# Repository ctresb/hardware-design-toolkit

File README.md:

<p align="center">
  <a href="#install">Install</a> ·
  <a href="#how-it-works">How it works</a> ·
  <a href="#the-skills">Skills</a> ·
  <a href="examples/pocket-beacon">Example</a> ·
  <a href="CONVENTIONS.md">Conventions</a>
</p>

---

The Hardware Design Toolkit is a set of [Claude Code](https://code.claude.com) skills. They take an idea
for an electronic device to a design that a factory can build. You describe what you want. Claude
interviews you, picks real parts and checks that they can be bought. It sizes a battery that exists, lays
out the board in KiCad and models the enclosure in CAD. It validates that nothing collides, renders the
product, draws the blueprint and prices it from 1 to 10,000 units. It lists the certifications and plans
the prototypes. Then it attacks its own design until nothing fixable is left.

The output is a **READY TO BUILD** package:

- a routed board with fab files;
- a BOM that is in stock;
- enclosure STEP files;
- an assembly guide and a test plan;
- an `ORDER.md` that says what to upload where;
- a presentation that explains the product.

## Why

A beautiful render of a device is easy. It is harder to make a device that is real. In practice the
problems look like this:

- The battery in the render has twice the capacity that a real cell of that size can hold.
- The chip is "Active" at the distributor but still sampling at the manufacturer.
- The LED driver needs 2.5 V and sits on a 1.8 V rail.
- The microphone is bottom-port and the design has no hole.
- The board was never routed.

Every rule in this toolkit comes from a mistake like these, made and corrected while a real wearable was
designed. Each skill checks for those mistakes with a script, not with good intentions.

## Quick Start

1. Install the plugin in Claude Code (or clone the repository for any agent runtime):
   ```text
   /plugin marketplace add ctresb/hardware-design-toolkit
   /plugin install hardware-design@hardware-design-toolkit
   ```
2. Launch a hardware project in an empty folder:
   ```text
   /hardware-design:hardware-engineer I want to build a small Bluetooth tag that beeps when I lose my keys
   ```
3. Verify the reference example (`examples/pocket-beacon`) from the terminal:
   ```sh
   python3 skills/doability-review/scripts/doability_score.py --hw examples/pocket-beacon/hw
   python3 skills/build-package/scripts/selftest.py
   ```
   See [docs/hardening-and-dfm-gates.md](docs/hardening-and-dfm-gates.md) for the physics, electrical, RF, and CAD verification gates.

## Install

In Claude Code:

```text
/plugin marketplace add ctresb/hardware-design-toolkit
/plugin install hardware-design@hardware-design-toolkit
```

Then start a project in an empty folder:

```text
/hardware-design:hardware-engineer I want to build a small Bluetooth tag that beeps when I lose my keys
```

The first run checks your machine and offers to install what is missing (`toolchain-setup`). Nothing is
installed without your consent.

<details>
<summary>Manual install (copy the skills)</summary>

```sh
git clone https://github.com/ctresb/hardware-design-toolkit
cp -R hardware-design-toolkit/skills/* ~/.claude/skills/
```

Copy every skill folder. The skills call each other's scripts through relative paths.
</details>

### Software it uses

| Tool | Used for | Required |
|---|---|---|
| [KiCad](https://www.kicad.org) 9 or 10 | schematic, PCB, DRC, fab outputs | yes, for PCB stages |
| [Freerouting](https://github.com/freerouting/freerouting) + Java 21+ | autorouting | for routing |
| [Blender](https://www.blender.org) 5.x | assembly validation, renders, blueprints | yes, for visual stages |
| [build123d](https://github.com/gumyr/build123d) (Python 3.10–3.13) | parametric enclosure CAD, STEP export | yes, for enclosure stages |
| Python 3.10+ | all scripts | yes |
| librsvg (`rsvg-convert`) | SVG to PDF/PNG | yes |
| Chrome or Chromium | presentation layout check and PDF | recommended |
| KiKit, FreeCAD, ffmpeg, ImageMagick | panels, STEP viewing, turntables, photos | optional |
| AWS CLI + Session Manager plugin | cloud GPU rendering | optional |

`toolchain-setup` installs these on macOS (Homebrew), Linux (apt, dnf or Flatpak) and Windows (winget).
It then writes the resolved paths to `toolchain.json` for the other skills.

## How it works

### Architecture

```mermaid
flowchart LR
  A[Interview] --> B[Specs and parts]
  B --> C[Part research]
  B --> D[Power and battery]
  C --> E{Paper review}
  D --> E
  E --> F[Enclosure CAD]
  E --> G[PCB]
  F <--> G
  F --> H{Assembly validation}
  G --> H
  H --> I[Renders and blueprint]
  H --> J[Cost, certification, roadmap]
  I --> K{Final review and fix loop}
  J --> K
  K -->|fixable findings| B
  K --> L[Build package]
  L --> M[Presentation]
```

All skills share one workspace in your project, `hw/`. Each file there has exactly one owner skill, and
every number carries its evidence: `verified` with a dated source, `estimate` with its basis, or
`assumption`. The contract is in [CONVENTIONS.md](CONVENTIONS.md).

Gates stop the pipeline when something is wrong:

- an unbuyable part;
- a rail outside a chip's supply range;
- a collision in the assembly;
- an unrouted board;
- a chart label crossing a line.

A finding that the toolkit can fix goes back to the skill that owns it, and the review runs again. Only
items that need you or the physical world stay open, for example a current measurement on the first
prototype. Each one comes with a method and a pass threshold.

## The skills

| Skill | What it does |
|---|---|
| [`hardware-engineer`](skills/hardware-engineer) | Leads the project: stages, gates, parallel work, the fix loop, state |
| [`product-discovery`](skills/product-discovery) | Interviews you about use, environment, size, power, markets and budget, and writes the brief |
| [`specs-engineer`](skills/specs-engineer) | Requirements, architecture, power rails and a part for every function; lints the BOM |
| [`electronics-researcher`](skills/electronics-researcher) | One dossier per part: datasheet facts, max dimensions, lifecycle, prices from 1 to 10k, stock, alternatives |
| [`battery-and-power`](skills/battery-and-power) | Power budget per mode, peak-current chain, and the largest real cell that fits your space |
| [`pcb-engineer`](skills/pcb-engineer) | Generates the KiCad schematic and board from a spec, with legalized placement and keepouts, ERC/DRC, routing and fab outputs |
| [`enclosure-engineer`](skills/enclosure-engineer) | build123d enclosure with DFM checks, STEP export, tolerance stack, sealing; validates the assembly in Blender |
| [`product-render`](skills/product-render) | Photoreal Cycles renders: studio recipes, worn materials, physical solder fillets, cloud GPU guide |
| [`technical-drawing`](skills/technical-drawing) | Vector exploded blueprint with BOM balloons and orthographic views with dimensions |
| [`cost-and-sourcing`](skills/cost-and-sourcing) | Unit cost from 1 to 10k units, one-time costs separated, landed cost per country, suppliers, RFQs |
| [`compliance-planner`](skills/compliance-planner) | Certifications per market (radio, battery, safety, privacy) with cost and lead time |
| [`prototype-roadmap`](skills/prototype-roadmap) | Dev kit to EVT, DVT, PVT and mass production, with the critical path and long-lead orders |
| [`doability-review`](skills/doability-review) | The red team: checks everything again, sends fixes to their owners, and gives the final verdict |
| [`build-package`](skills/build-package) | Assembles the release (fab, assembly, purchasing, mech, test, order steps) and runs the ready-to-build gate |
| [`product-presentation`](skills/product-presentation) | A self-contained HTML deck of the product, with an automated layout check |
| [`lab-notebook`](skills/lab-notebook) | Facts, experiments, lessons and retros, so the project never goes backwards |
| [`toolchain-setup`](skills/toolchain-setup) | Finds, installs and verifies the software |

You can run any skill alone, for example `/hardware-design:doability-review` on a design you already have.

## Example

[`examples/pocket-beacon`](examples/pocket-beacon) is a complete run of the toolkit on a fictional
Bluetooth item finder that runs on a CR2032. It ends **READY TO BUILD (prototype)**:

- a routed 4-layer board with fab files;
- a 32 × 32 × 10 mm enclosure in STEP;
- 47 parts in stock with dated prices;
- a cost model from 10 to 10,000 units;
- a certification plan, a roadmap and a release package with the ordering steps.

The run also improved the toolkit. Each skill bug and missing rule it hit was fixed in the skills
([`docs/integration-report.md`](docs/integration-report.md)).

## Principles

1. **Real before pretty.** Parts are sized by the datasheet's maximum dimensions, never the nominal ones.
   Cells have straight edges and seals. A placeholder never pretends to be the product.
2. **Measure before you commit.** No custom cell, mold or board revision without a measured power budget or
   a dated plan to measure it.
3. **Evidence on every number.** Estimates are labeled, and every estimate comes with the quote or
   measurement that would replace it.
4. **Validate before you show.** No render, drawing or slide comes from an assembly that did not pass the
   validator. No visual leaves without an automated layout check.
5. **Fix, don't report.** The toolkit fixes what it can and asks only about what it cannot.

## Limits

- The toolkit plans certifications. It does not certify anything, and nothing here is legal advice.
- Prices and stock are snapshots with dates. Check them again before you order.
- RF matching, acoustic tuning and the final power numbers need a real prototype and real instruments. The
  toolkit tells you exactly what to measure and the pass values.
- **WARNING** Lithium cells can catch fire when punctured, shorted or charged wrong. Mains-powered designs
  can kill. Follow the safety notes in the skills, and have a qualified person review designs that involve
  either.

## Contributing

Read [CONVENTIONS.md](CONVENTIONS.md) first. A new rule needs the mistake that motivated it. A new script
needs a test that fails without it.

## License

[MIT](LICENSE). This is an independent community project, not affiliated with or endorsed by Anthropic.
"Claude" and "Claude Code" are trademarks of Anthropic.

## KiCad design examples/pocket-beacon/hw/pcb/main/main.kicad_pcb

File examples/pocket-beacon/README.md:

# Pocket Beacon: a complete run of the toolkit

Pocket Beacon is a fictional Bluetooth item finder for keys and bags. It beeps when the phone asks, runs
for more than a year on a CR2032, and is sealed to IP67. Every file in `hw/` was produced by the toolkit's
skills in one session: interview decisions, part research, power, KiCad board, CAD enclosure, validation,
renders, drawings, cost, certification, roadmap, review and release.

**Verdict: READY TO BUILD (prototype).** The board is routed and the fab files pass the release check. The
enclosure is in STEP and the assembly validates. 15 measurements remain for the built prototype, each with
a method and a pass threshold.

| | |
|---|---|
| Size | 32.0 × 32.0 × 10.0 mm, 4.3 g of plastic |
| Radio | TI CC2340R52 BLE SoC, chip antenna |
| Sound | Same Sky CPT-9019A piezo with PAM8904 driver, ≈ 78–80 dB at 25 cm [estimate] |
| Battery | CR2032 in a Keystone 3034TR holder, user-replaceable behind a tool-secured door (UL 4200A) |
| Battery life | 13 months calibrated on real trackers, 35 months bottom-up [estimate] |
| Board | 28.4 mm, 4 layers, 0.6 mm, 47 parts, DRC 0, ERC 0, every part with an LCSC number except the cell |
| Unit cost | US$ 51–153 at 10 units, US$ 8.89–17.1 at 1,000 units (FOB) |
| 10 EVT prototypes | US$ 800–1,800 in total, steps in [`ORDER.md`](hw/release/evt0-a/ORDER.md) |
| Certification | US$ 33k–128.5k for US, EU, UK and Brazil [estimate]; US first |
| First legal US sale | between 2027-05-10 and 2027-09-27 |

## What the toolkit found and fixed

The first parts list looked fine on paper. Research and review changed it:

- **4 of 23 first-choice parts could not be used.**
  - The piezo was last-time-buy.
  - The 48 MHz crystal had 4 units in stock.
  - An RF inductor was obsolete.
  - Two capacitors had no stock.
- **The 22 µF bulk capacitors keep 10.7 µF at 3 V.** A third capacitor was added to meet TI's
  supply-slew limit during the ring.
- **A loud ring on a cold, aged CR2032 browns out the chip.** The firmware rule now picks the ring level
  from the cell voltage under load.
- **Comparison with TI's reference board** found a missing VDDD capacitor and a missing harmonic filter.
- **A coin-cell bayonet did not fit in 10 mm.** The door uses captive screws instead, which still meets
  the US coin-cell law.
- **Assembler catalogs list look-alike parts under genuine part numbers.** Parts are ordered by catalog
  number, and the brand is checked.

## Where to look

| Folder | Content |
|---|---|
| [`hw/brief.md`](hw/brief.md), [`requirements.md`](hw/requirements.md), [`architecture.md`](hw/architecture.md) | What it is and how it works |
| [`hw/bom.csv`](hw/bom.csv), [`hw/parts/`](hw/parts) | The BOM and one dossier per part, with sources and dates |
| [`hw/power/`](hw/power) | Power budget, CR2032 behavior, measurement plan |
| [`hw/pcb/`](hw/pcb) | KiCad project, fab outputs, plots |
| [`hw/mech/`](hw/mech) | build123d CAD, STEP/STL, DFM, tolerances, validated assembly |
| [`hw/renders/`](hw/renders), [`hw/drawings/`](hw/drawings) | Cycles renders and the quotation blueprint |
| [`hw/cost/`](hw/cost), [`hw/compliance.md`](hw/compliance.md), [`hw/roadmap.md`](hw/roadmap.md) | Business |
| [`hw/doability/review.md`](hw/doability/review.md) | The adversarial review and the prototype checks |
| [`hw/release/evt0-a/`](hw/release/evt0-a) | The READY TO BUILD package |
| [`hw/presentation/index.html`](hw/presentation/index.html) | The presentation |
| [`hw/knowledge/`](hw/knowledge), [`hw/decisions.md`](hw/decisions.md), [`hw/retros/`](hw/retros) | How every decision was made |

## What is still open

- **Decisions taken in the product-owner role.** Each one is logged in `hw/decisions.md` for a real
  owner to confirm. Examples: the screw door, and launching in the US first.
- **Quotes.** Final assembly and molding costs decide whether the US$ 12 target at 1,000 units is met
  (`hw/cost/rfq.md`).
- **The 15 prototype measurements:** current, RF match, loudness, sealing and button continuity
  (`hw/doability/review.md`).

Pocket Beacon is fictional. Prices and stock are snapshots from 2026-11-08.

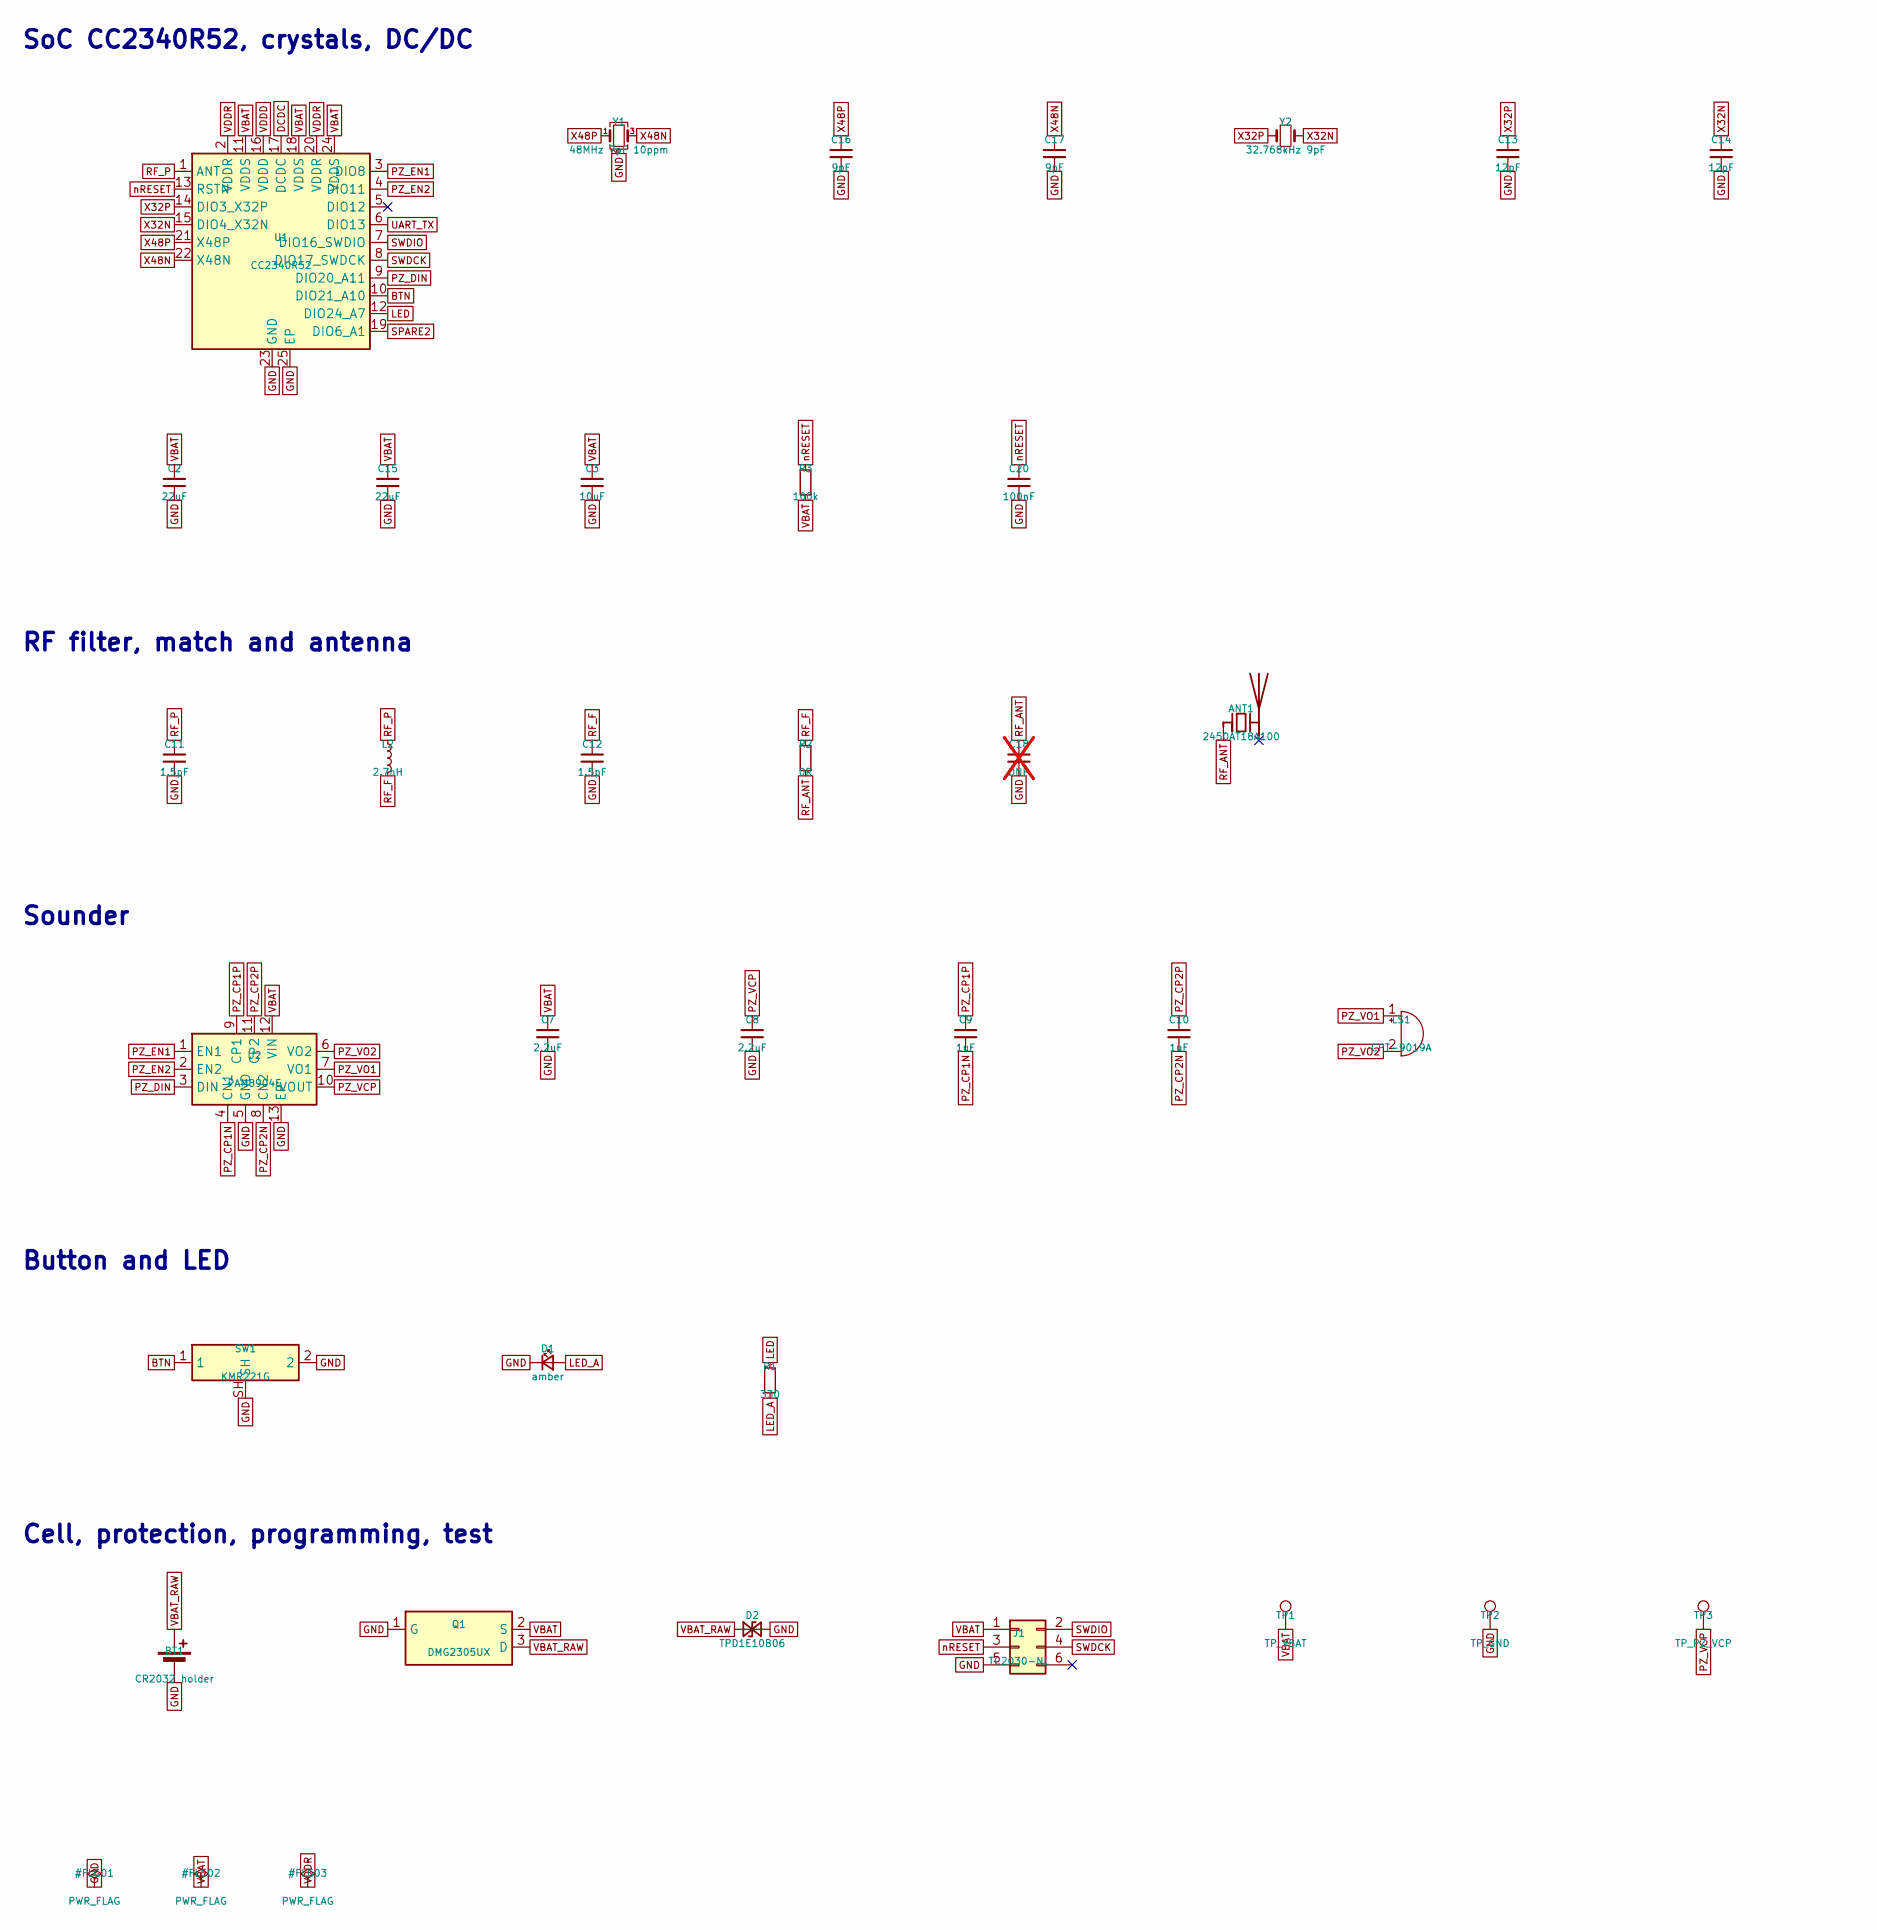
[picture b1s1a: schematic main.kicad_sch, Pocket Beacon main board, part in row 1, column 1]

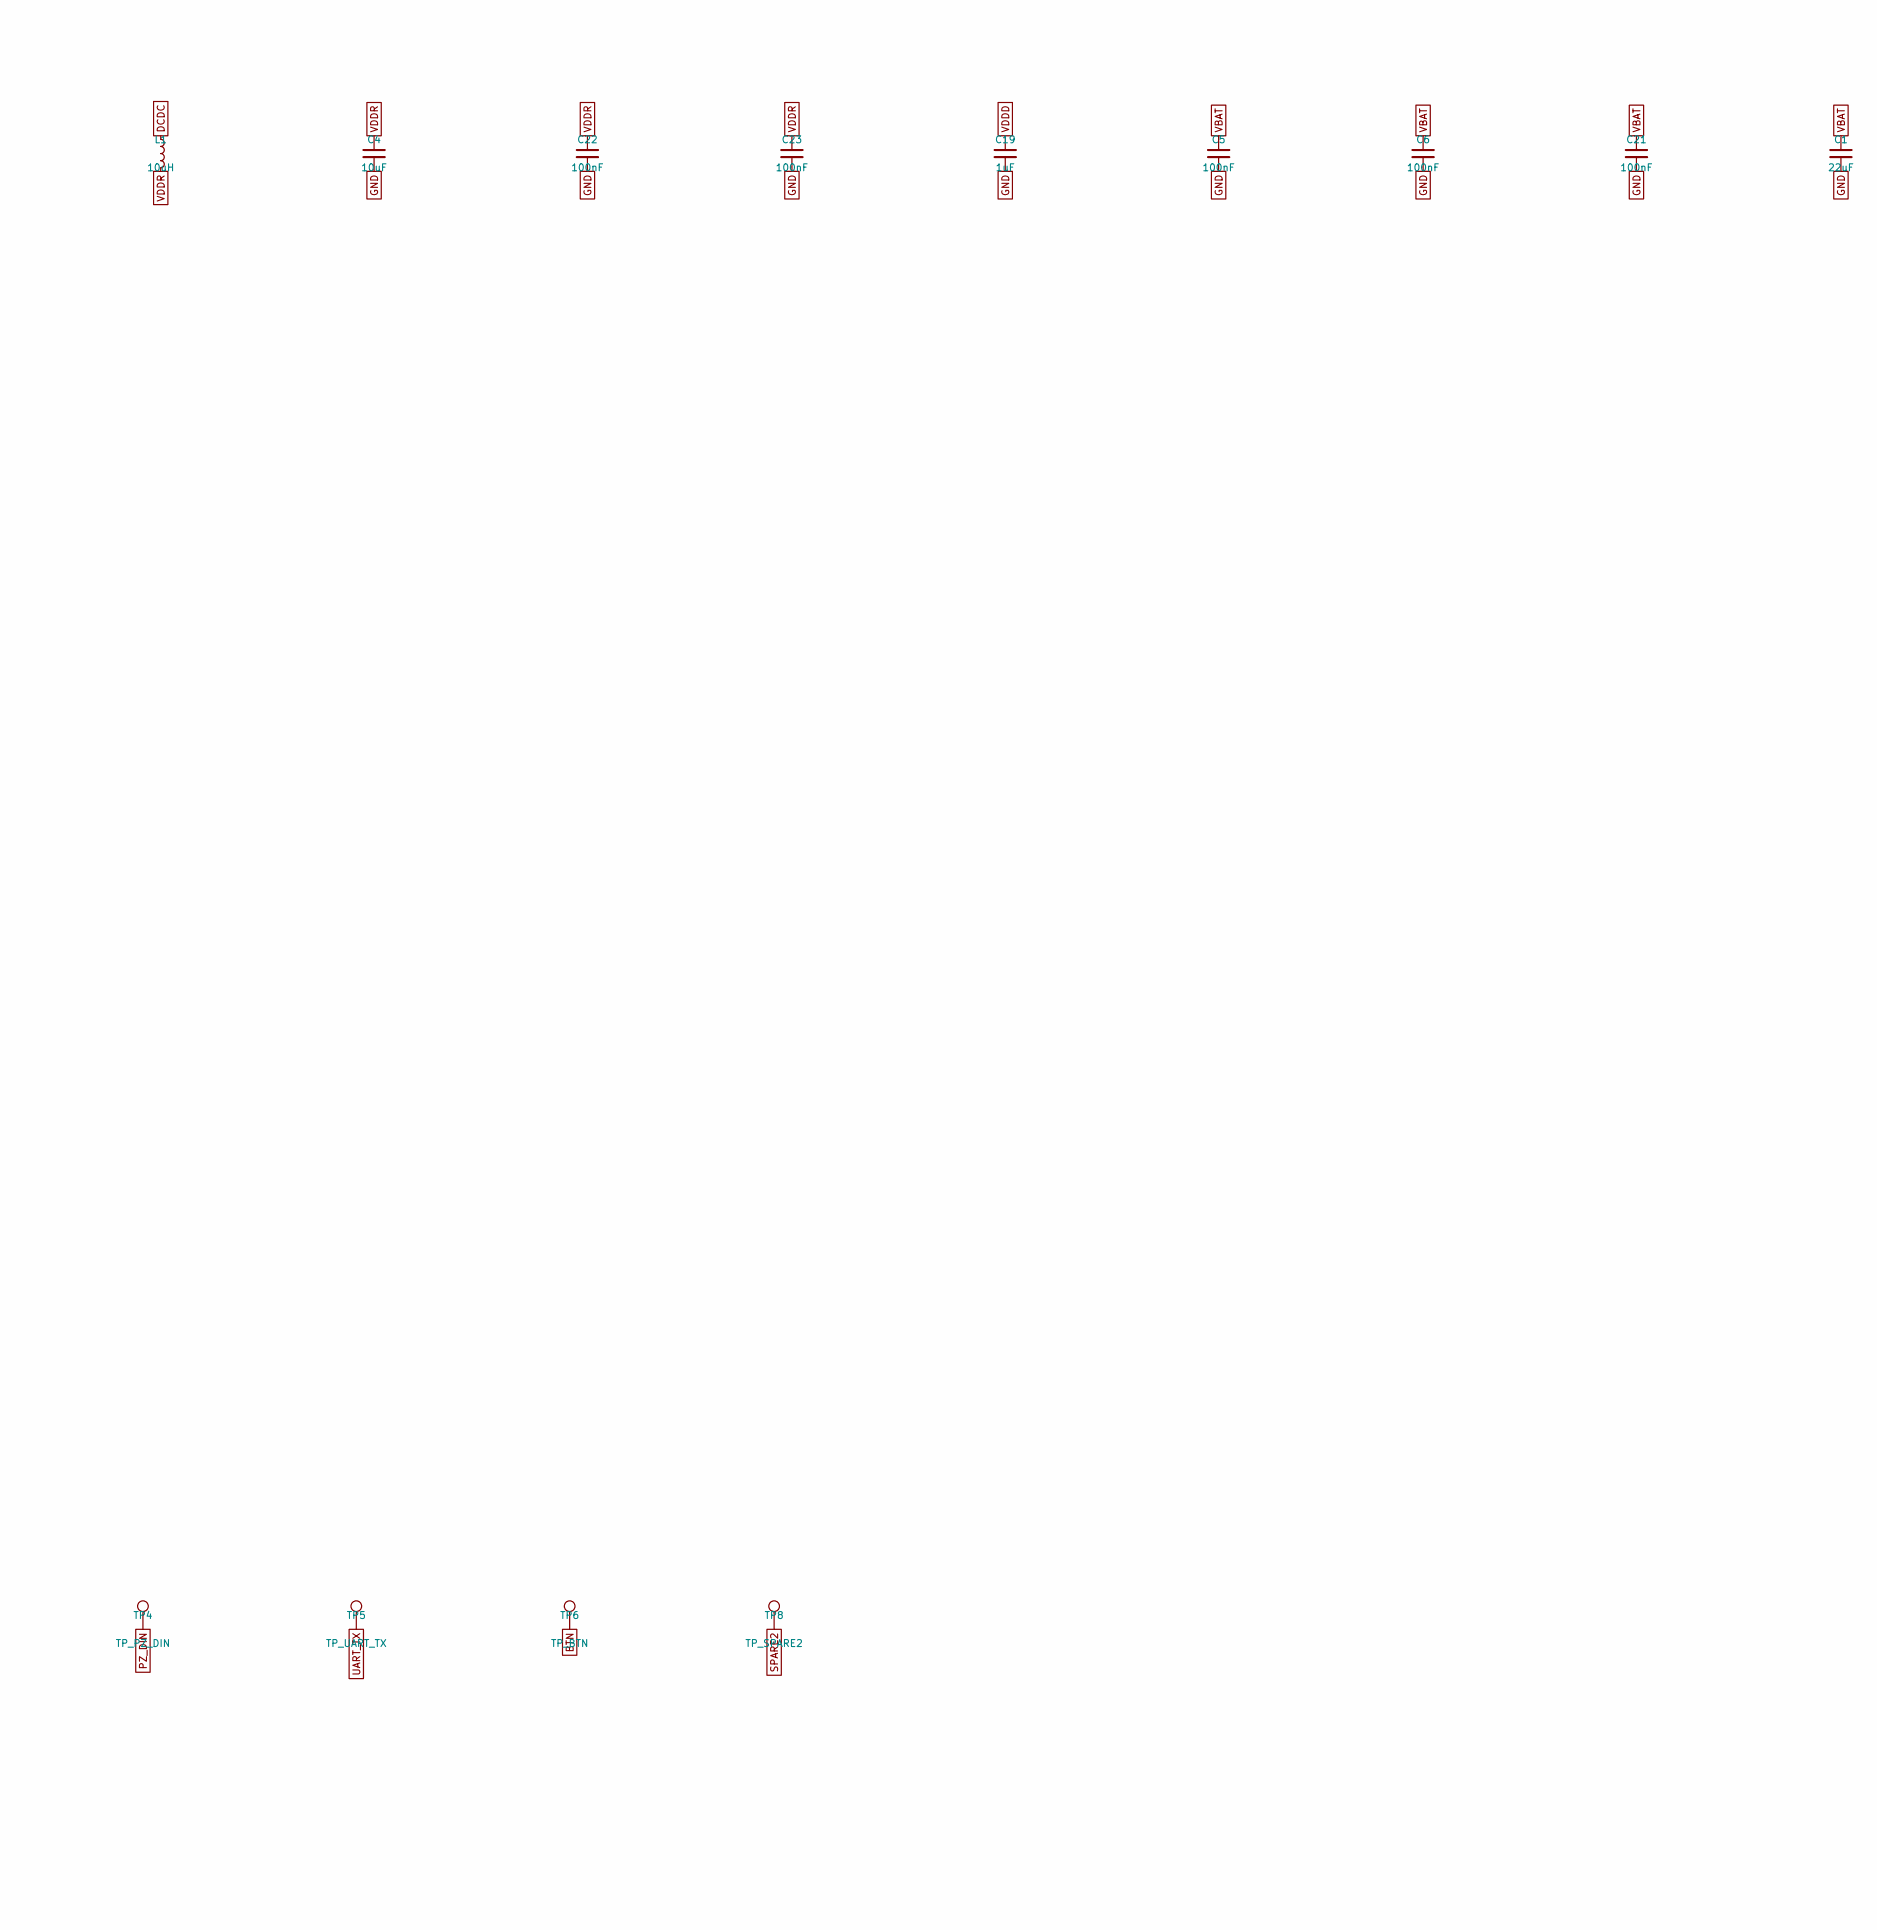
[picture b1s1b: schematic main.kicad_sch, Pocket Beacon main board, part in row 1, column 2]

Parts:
ANT1: 2450AT18A100; Johanson_2450AT18x100; MPN 2450AT18A0100001E; LCSC C17430588
BT1: CR2032 holder; BatteryHolder_Keystone_3034_1x20mm; MPN 3034TR; LCSC C5213768
C1, C2, C15: 22uF; C_0603_1608Metric; MPN CL10A226MQ8NRNC; LCSC C59461
C3, C4: 10uF; C_0603_1608Metric; MPN CL10A106KP8NNNC; LCSC C19702
C5, C6, C20, C21, C22, C23: 100nF; C_0402_1005Metric; MPN CL05B104KO5NNNC; LCSC C1525
C7, C8: 2.2uF; C_0603_1608Metric; MPN CL10A225KO8NNNC; LCSC C23630
C9, C10, C19: 1uF; C_0402_1005Metric; MPN CL05A105KA5NQNC; LCSC C52923
C11, C12: 1.5pF; C_0402_1005Metric; MPN GJM1555C1H1R5BB01D; LCSC C76900
C13, C14: 12pF; C_0402_1005Metric; MPN 0402CG120J500NT; LCSC C1547
C16, C17: 9pF; C_0402_1005Metric; MPN 0402CG9R0C500NT; LCSC C1580
C18: DNP; C_0402_1005Metric; not fitted
D1: amber; LED_0603_1608Metric; MPN LTST-C191KFKT; LCSC C160478
D2: TPD1E10B06; TI_DPY0002A_X1SON2; MPN TPD1E10B06DPYR; LCSC C48260
J1: TC2030-NL; Tag-Connect_TC2030-IDC-NL_2x03_P1.27mm_Vertical
L1: 10uH; L_0805_2012Metric; MPN MLZ2012M100WT000; LCSC C88173
L2: 2.7nH; L_0402_1005Metric; MPN LQG15HS2N7B02D; LCSC C162541
LS1: CPT-9019A; SAMESKY_CPT9019A_SMT; MPN CPT-9019A-SMT-TR; LCSC C20181991
Q1: DMG2305UX; SOT-23-3; MPN DMG2305UX-7; LCSC C150470
R1: 330; R_0402_1005Metric; MPN 0402WGF3300TCE; LCSC C25104
R2: 0R; R_0402_1005Metric; MPN 0402WGF0000TCE; LCSC C17168
R3: 100k; R_0402_1005Metric; MPN 0402WGF1003TCE; LCSC C25741
SW1: KMR221G; SW_Push_1P1T-SH_NO_CK_KMR2xxG; MPN KMR221GLFS; LCSC C72443
TP1: TP_VBAT; TestPoint_Pad_D1.0mm
TP2: TP_GND; TestPoint_Pad_D1.0mm
TP3: TP_PZ_VCP; TestPoint_Pad_D1.0mm
TP4: TP_PZ_DIN; TestPoint_Pad_D1.0mm
TP5: TP_UART_TX; TestPoint_Pad_D1.0mm
TP6: TP_BTN; TestPoint_Pad_D1.0mm
TP8: TP_SPARE2; TestPoint_Pad_D1.0mm
U1: CC2340R52; TI_RGE0024B_VQFN24_4x4_P0.5; MPN CC2340R52E0RGER; LCSC C20416850
U2: PAM8904E; DIODES_WQFN2020_12_US; MPN PAM8904EGPR; LCSC C510550
Y1: 48MHz 7pF 10ppm; Crystal_SMD_2016-4Pin_2.0x1.6mm; MPN ABM11W-48.0000MHZ-7-B1U-T3; LCSC C1985532
Y2: 32.768kHz 9pF; Crystal_SMD_2012-2Pin_2.0x1.2mm; MPN ABS06-32.768KHZ-9-T; LCSC C1985410

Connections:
BTN: SW1.1, TP6.1, U1.10 (DIO21_A10)
DCDC: L1.1, U1.17 (DCDC)
GND: BT1.2 (-), C1.2, C2.2, C3.2, C4.2, C5.2, C6.2, C7.2, C8.2, C11.2, C12.2, C13.2, C14.2, C15.2, C16.2, C17.2, C18.2, C19.2, C20.2, C21.2, C22.2, C23.2, D1.1 (K), D2.2 (A2), J1.5, Q1.1 (G), SW1.2, SW1.SH, TP2.1, U1.23 (GND), U1.25 (EP), U2.5 (GND), U2.13 (EP), Y1.2 (G), Y1.4 (G)
LED: R1.1, U1.12 (DIO24_A7)
LED_A: D1.2 (A), R1.2
PZ_CP1N: C9.2, U2.4 (CN1)
PZ_CP1P: C9.1, U2.9 (CP1)
PZ_CP2N: C10.2, U2.8 (CN2)
PZ_CP2P: C10.1, U2.11 (CP2)
PZ_DIN: TP4.1, U1.9 (DIO20_A11), U2.3 (DIN)
PZ_EN1: U1.3 (DIO8), U2.1 (EN1)
PZ_EN2: U1.4 (DIO11), U2.2 (EN2)
PZ_VCP: C8.1, TP3.1, U2.10 (VOUT)
PZ_VO1: LS1.1 (+), U2.7 (VO1)
PZ_VO2: LS1.2 (-), U2.6 (VO2)
RF_ANT: ANT1.1 (FEED), C18.1, R2.2
RF_F: C12.1, L2.2, R2.1
RF_P: C11.1, L2.1, U1.1 (ANT)
SPARE2: TP8.1, U1.19 (DIO6_A1)
SWDCK: J1.4, U1.8 (DIO17_SWDCK)
SWDIO: J1.2, U1.7 (DIO16_SWDIO)
UART_TX: TP5.1, U1.6 (DIO13)
VBAT: C1.1, C2.1, C3.1, C5.1, C6.1, C7.1, C15.1, C21.1, J1.1, Q1.2 (S), R3.2, TP1.1, U1.11 (VDDS), U1.18 (VDDS), U1.24 (VDDS), U2.12 (VIN)
VBAT_RAW: BT1.1 (+), D2.1 (A1), Q1.3 (D)
VDDD: C19.1, U1.16 (VDDD)
VDDR: C4.1, C22.1, C23.1, L1.2, U1.2 (VDDR), U1.20 (VDDR)
X32N: C14.1, U1.15 (DIO4_X32N), Y2.2
X32P: C13.1, U1.14 (DIO3_X32P), Y2.1
X48N: C17.1, U1.22 (X48N), Y1.3
X48P: C16.1, U1.21 (X48P), Y1.1
nRESET: C20.1, J1.3, R3.1, U1.13 (RSTN)

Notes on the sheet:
SoC CC2340R52, crystals, DC/DC
RF filter, match and antenna
Sounder
Button and LED
Cell, protection, programming, test

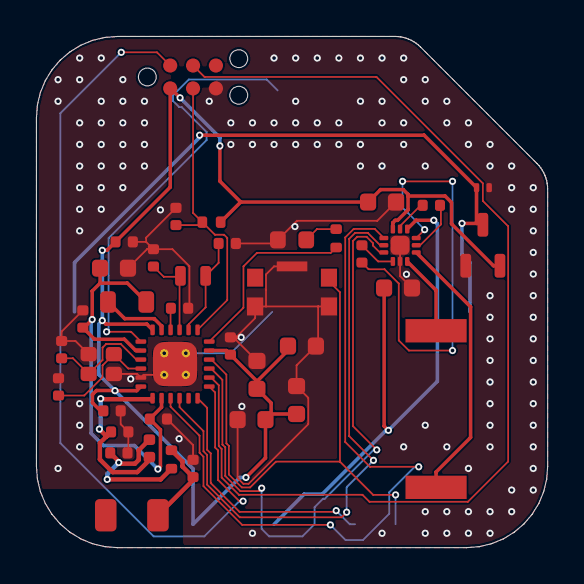
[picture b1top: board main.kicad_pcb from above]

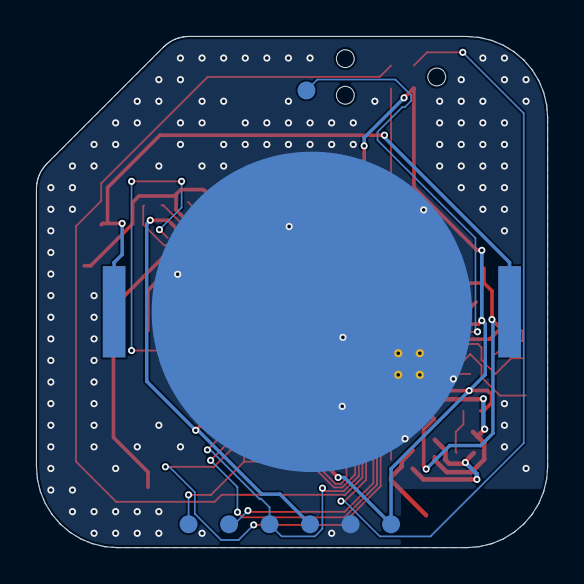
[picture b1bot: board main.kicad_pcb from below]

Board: 4 copper layers, 28.4 x 28.4 mm, 47 parts (8 on the bottom side), 31 nets.
